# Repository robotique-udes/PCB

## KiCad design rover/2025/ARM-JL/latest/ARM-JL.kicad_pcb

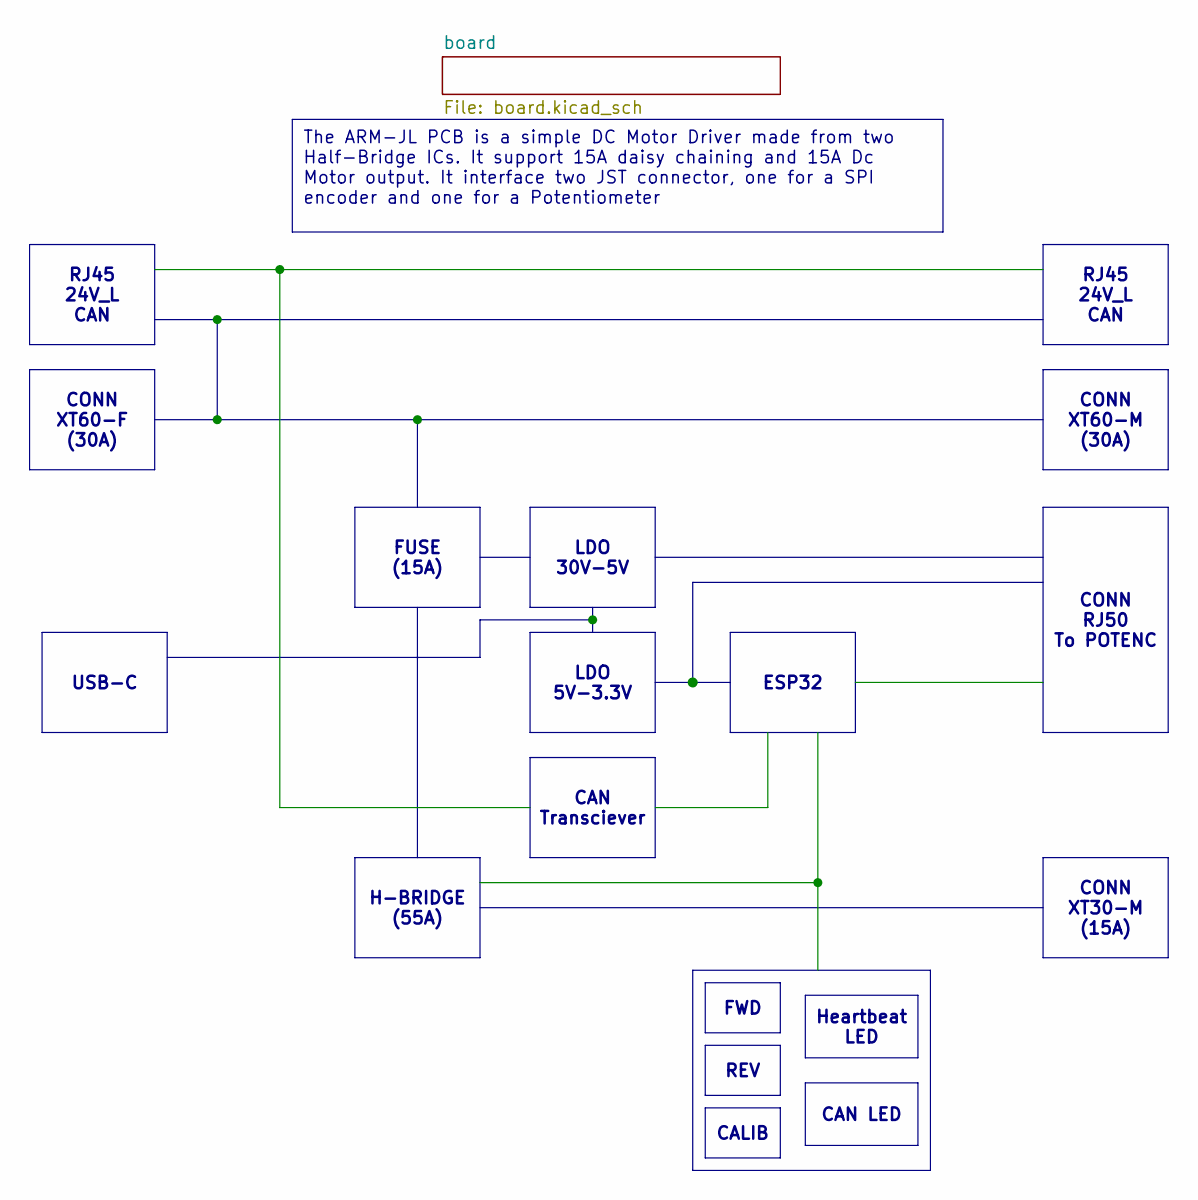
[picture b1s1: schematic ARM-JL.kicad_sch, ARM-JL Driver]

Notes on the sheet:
LDO 30V-5V
REV
CONN XT60-M (30A)
FWD
RJ45 24V_L CAN
FUSE (15A)
CAN LED
H-BRIDGE (55A)
Heartbeat LED
CONN XT60-F (30A)
CAN Transciever
USB-C
CONN RJ50 To POTENC
The ARM-JL PCB is a simple DC Motor Driver made from two Half-Bridge ICs. It support 15A daisy chaining and 15A Dc Motor output. It interface two JST connector, one for a SPI encoder and one for a Potentiometer
LDO 5V-3.3V
CALIB
ESP32
CONN XT30-M (15A)

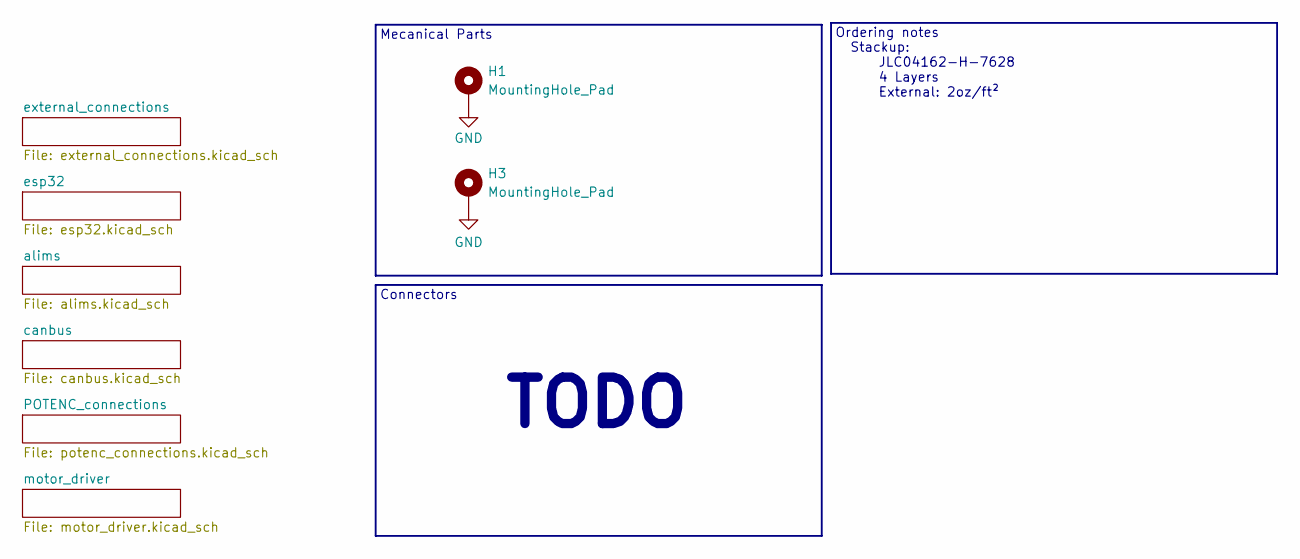
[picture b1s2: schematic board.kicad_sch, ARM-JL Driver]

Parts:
H1, H3: MountingHole_Pad; MountingHole_3.2mm_M3_DIN965_Pad_TopBottom

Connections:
GND: H1.1, H3.1; also elsewhere on the board

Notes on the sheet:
TODO
Mecanical Parts
Stackup: JLC04162-H-7628 4 Layers External: 2oz/ft²
Connectors
Ordering notes

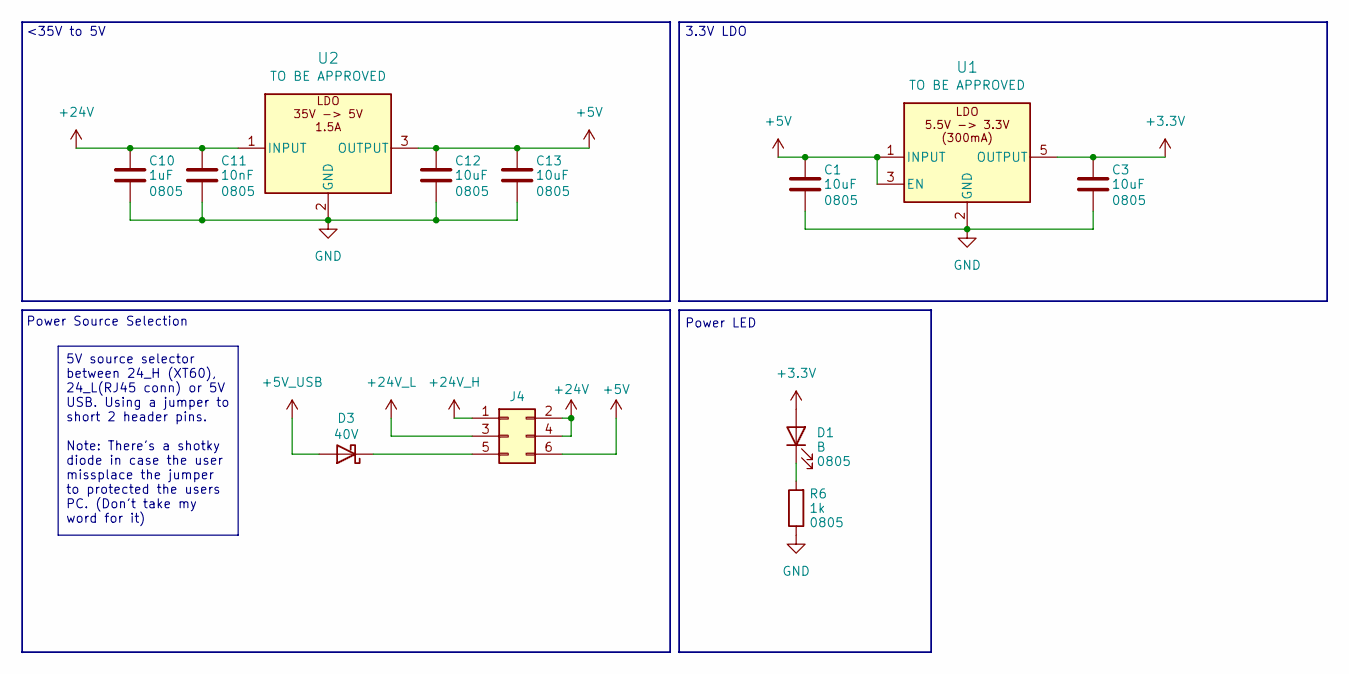
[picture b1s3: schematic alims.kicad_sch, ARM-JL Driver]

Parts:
C1, C3, C12, C13: 10uF; C_0805_2012Metric_Pad1.18x1.45mm_HandSolder
C10: 1uF; C_0805_2012Metric_Pad1.18x1.45mm_HandSolder
C11: 10nF; C_0805_2012Metric_Pad1.18x1.45mm_HandSolder
D1: B; LED_0805_2012Metric_Pad1.15x1.40mm_HandSolder
D3: 40V; D_SMA
J4: Conn_02x03_Odd_Even; PinHeader_2x03_P2.54mm_Vertical_SMD
R6: 1k; R_0805_2012Metric_Pad1.20x1.40mm_HandSolder
U1: LDO-TLV74033PDBVR; SOT-23-5_HandSoldering
U2: LDO-LM7805MPX/NOPB; SOT-223-3_TabPin2

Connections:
+5V: C1.1, C12.1, C13.1, J4.6, U1.1 (INPUT), U1.3 (EN), U2.3 (OUTPUT); also elsewhere on the board
+5V_USB: D3.2 (A); also elsewhere on the board
+24V: C10.1, C11.1, J4.2, J4.4, U2.1 (INPUT)
+24V_H: J4.1; also elsewhere on the board
+24V_L: J4.3; also elsewhere on the board
GND: C1.2, C3.2, C10.2, C11.2, C12.2, C13.2, R6.1, U1.2 (GND), U2.2 (GND); also elsewhere on the board
unnamed: D1.1 (K), R6.2
unnamed: D3.1 (K), J4.5

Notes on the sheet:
5V source selector between 24_H (XT60), 24_L(RJ45 conn) or 5V USB. Using a jumper to short 2 header pins. Note: There's a shotky diode in case the user missplace the jumper to protected the users PC. (Don't take my word for it)
3.3V LDO
Power LED
<35V to 5V
Power Source Selection

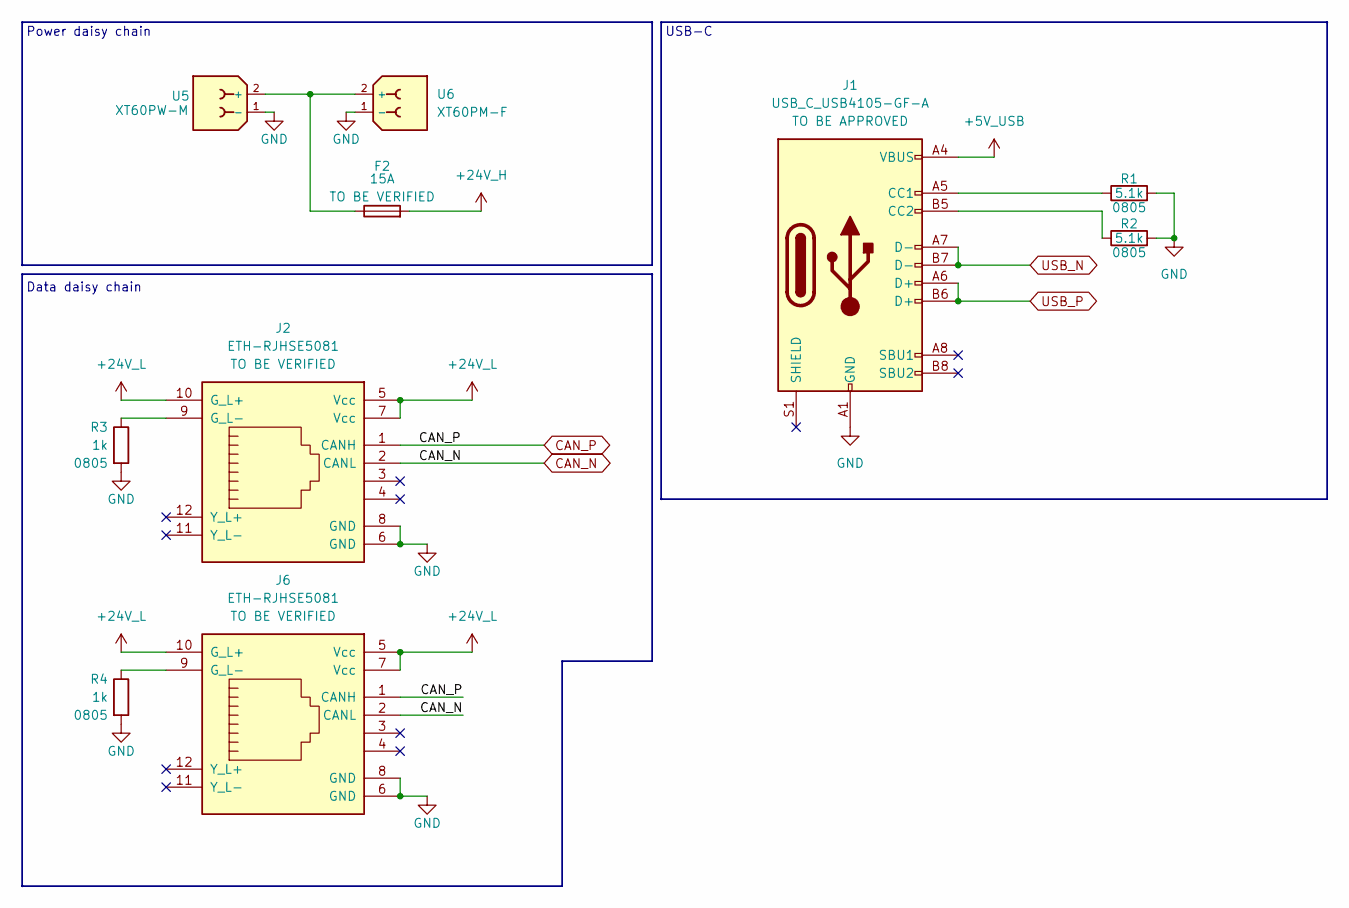
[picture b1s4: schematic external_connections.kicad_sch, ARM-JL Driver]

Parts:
F2: 15A; FuseHolder-3588-20
J1: USB_C_USB4105-GF-A; USB4145_GCT
J2, J6: ETH-RJHSE5081
R1, R2: 5.1k; R_0805_2012Metric_Pad1.20x1.40mm_HandSolder
R3, R4: 1k; R_0805_2012Metric_Pad1.20x1.40mm_HandSolder
U5: XT60PW-M; AMASS_XT60PW-M_1x02_P7.20mm_Horizontal
U6: XT60PM-F; AMASS_XT60PW-F_1x02_P7.20mm_Horizontal

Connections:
+5V_USB: J1.A4 (VBUS), J1.A9 (VBUS), J1.B4 (VBUS), J1.B9 (VBUS); also elsewhere on the board
+24V_H: F2.1; also elsewhere on the board
+24V_L: J2.5 (Vcc), J2.7 (Vcc), J2.10 (G_L+), J6.5 (Vcc), J6.7 (Vcc), J6.10 (G_L+); also elsewhere on the board
CAN_N: J2.2 (CANL), J6.2 (CANL); also elsewhere on the board
CAN_P: J2.1 (CANH), J6.1 (CANH); also elsewhere on the board
GND: J1.A1 (GND), J1.A12 (GND), J1.B1 (GND), J1.B12 (GND), J2.6 (GND), J2.8 (GND), J6.6 (GND), J6.8 (GND), R1.2, R2.2, R3.2, R4.2, U5.1 (-), U6.1 (-); also elsewhere on the board
unnamed: J1.A5 (CC1), R1.1
unnamed: J1.B5 (CC2), R2.1
unnamed: J2.9 (G_L-), R3.1
unnamed: J6.9 (G_L-), R4.1
unnamed: F2.2, U5.2 (+), U6.2 (+)
USB_N: J1.A7 (D-), J1.B7 (D-); also elsewhere on the board
USB_P: J1.A6 (D+), J1.B6 (D+); also elsewhere on the board

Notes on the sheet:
Data daisy chain
USB-C
Power daisy chain

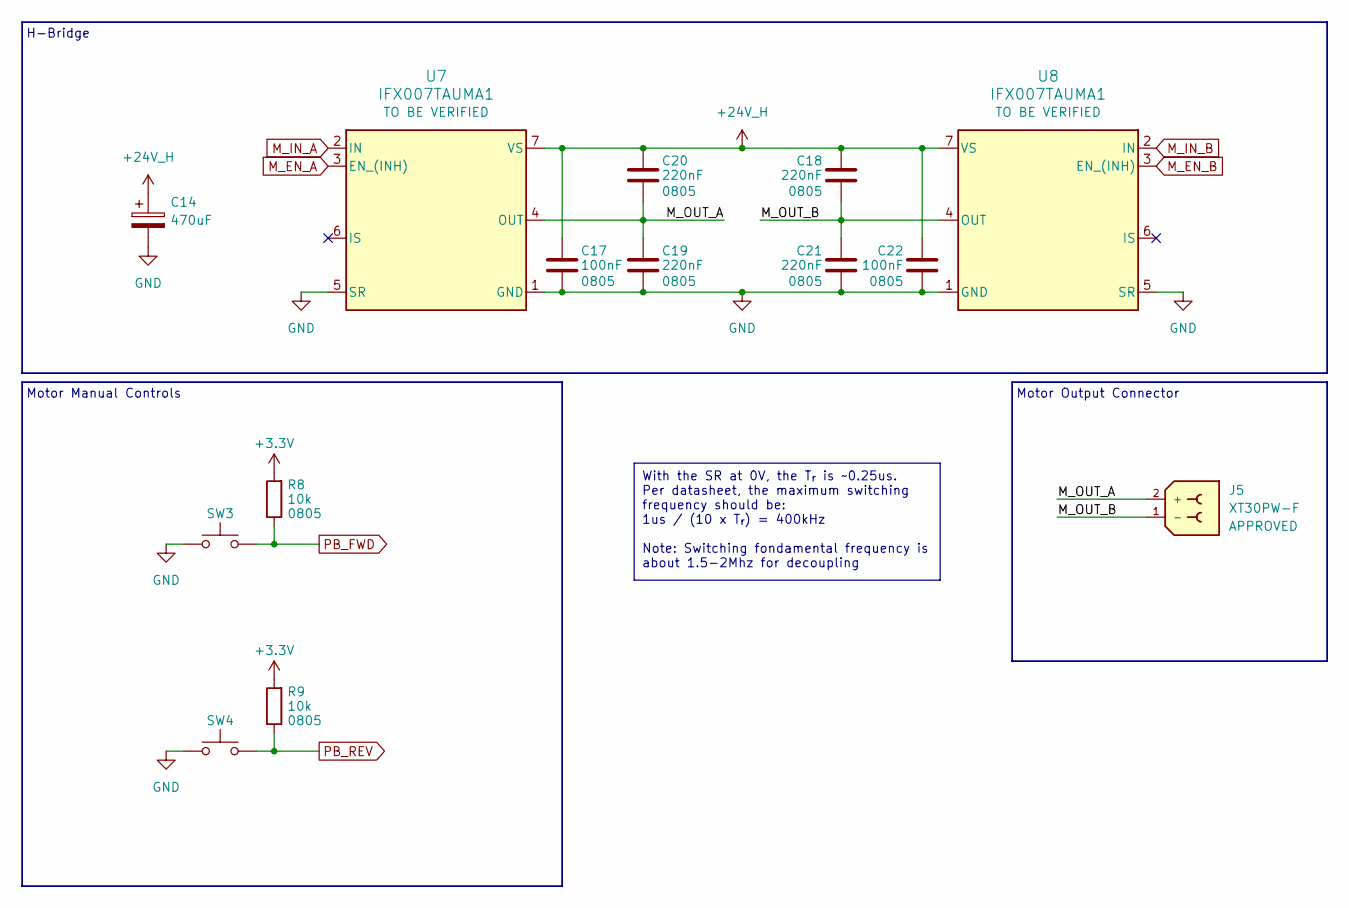
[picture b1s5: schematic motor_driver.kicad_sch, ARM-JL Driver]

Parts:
C14: 470uF; CP_Elec_10x12.6
C17, C22: 100nF; C_0805_2012Metric_Pad1.18x1.45mm_HandSolder
C18, C19, C20, C21: 220nF; C_0805_2012Metric_Pad1.18x1.45mm_HandSolder
J5: XT30PW-F; AMASS_XT30PW-F_1x02_P2.50mm_Horizontal; PARTREV 1.2
R8, R9: 10k; R_0805_2012Metric_Pad1.20x1.40mm_HandSolder
SW3, SW4: SW-PTS815SJM250SMTRLFS; SW-PTS815 SJM250SMTRLFS
U7, U8: IFX007TAUMA1; TO-263-7_TabPin4

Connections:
+24V_H: C14.1, C17.1, C18.1, C20.1, C22.1, U7.7 (VS), U8.7 (VS); also elsewhere on the board
/board/motor_driver/M_OUT_A: C19.1, C20.2, J5.2 (+), U7.4 (OUT)
/board/motor_driver/M_OUT_B: C18.2, C21.1, J5.1 (-), U8.4 (OUT)
GND: C14.2, C17.2, C19.2, C21.2, C22.2, SW3.1, SW3.2, SW4.1, SW4.2, U7.1 (GND), U7.5 (SR), U8.1 (GND), U8.5 (SR); also elsewhere on the board
M_EN_A: U7.3 (EN_(INH)); also elsewhere on the board
M_EN_B: U8.3 (EN_(INH)); also elsewhere on the board
M_IN_A: U7.2 (IN); also elsewhere on the board
M_IN_B: U8.2 (IN); also elsewhere on the board
PB_FWD: R8.1, SW3.4; also elsewhere on the board
PB_REV: R9.1, SW4.4; also elsewhere on the board

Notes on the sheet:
With the SR at 0V, the T_{r} is ~0.25us. Per datasheet, the maximum switching frequency should be: 1us / (10 x T_{r}) = 400kHz Note: Switching fondamental frequency is about 1.5-2Mhz for decoupling
Motor Manual Controls
H-Bridge
Motor Output Connector

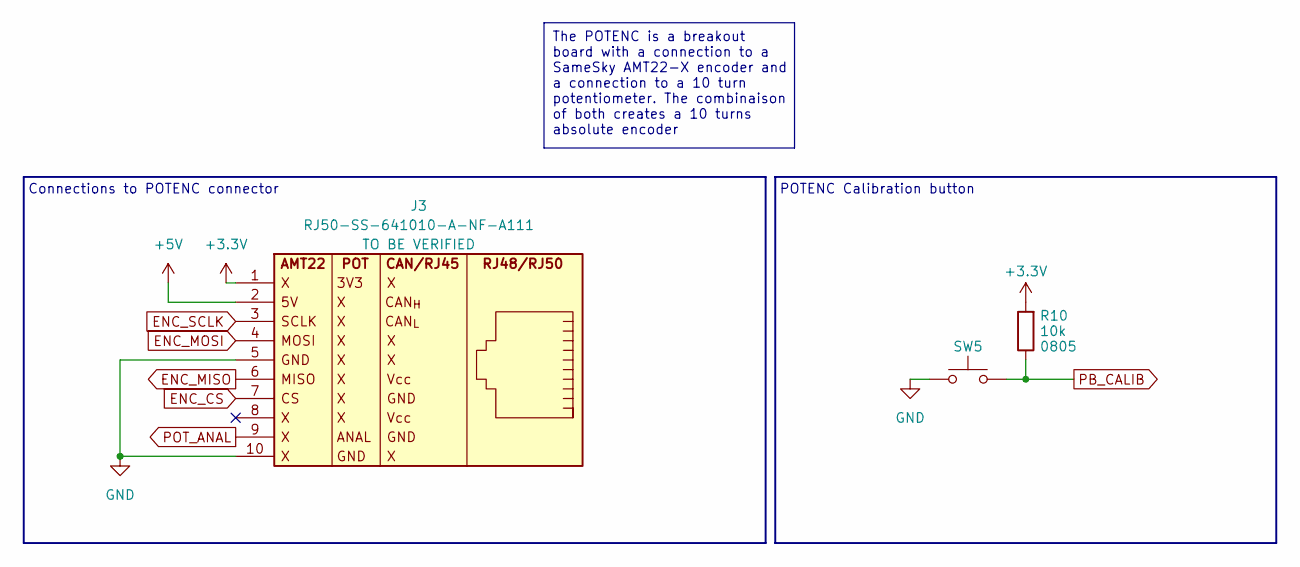
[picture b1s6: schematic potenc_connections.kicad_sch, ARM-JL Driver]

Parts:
J3: RJ50-SS-641010-A-NF-A111
R10: 10k; R_0805_2012Metric_Pad1.20x1.40mm_HandSolder
SW5: SW-PTS815SJM250SMTRLFS; SW-PTS815 SJM250SMTRLFS

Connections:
+5V: J3.2; also elsewhere on the board
ENC_CS: J3.7; also elsewhere on the board
ENC_MISO: J3.6; also elsewhere on the board
ENC_MOSI: J3.4; also elsewhere on the board
ENC_SCLK: J3.3; also elsewhere on the board
GND: J3.5, J3.10, SW5.1, SW5.2; also elsewhere on the board
PB_CALIB: R10.1, SW5.4; also elsewhere on the board
POT_ANAL: J3.9; also elsewhere on the board

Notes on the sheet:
The POTENC is a breakout board with a connection to a SameSky AMT22-X encoder and a connection to a 10 turn potentiometer. The combinaison of both creates a 10 turns absolute encoder
Connections to POTENC connector
POTENC Calibration button

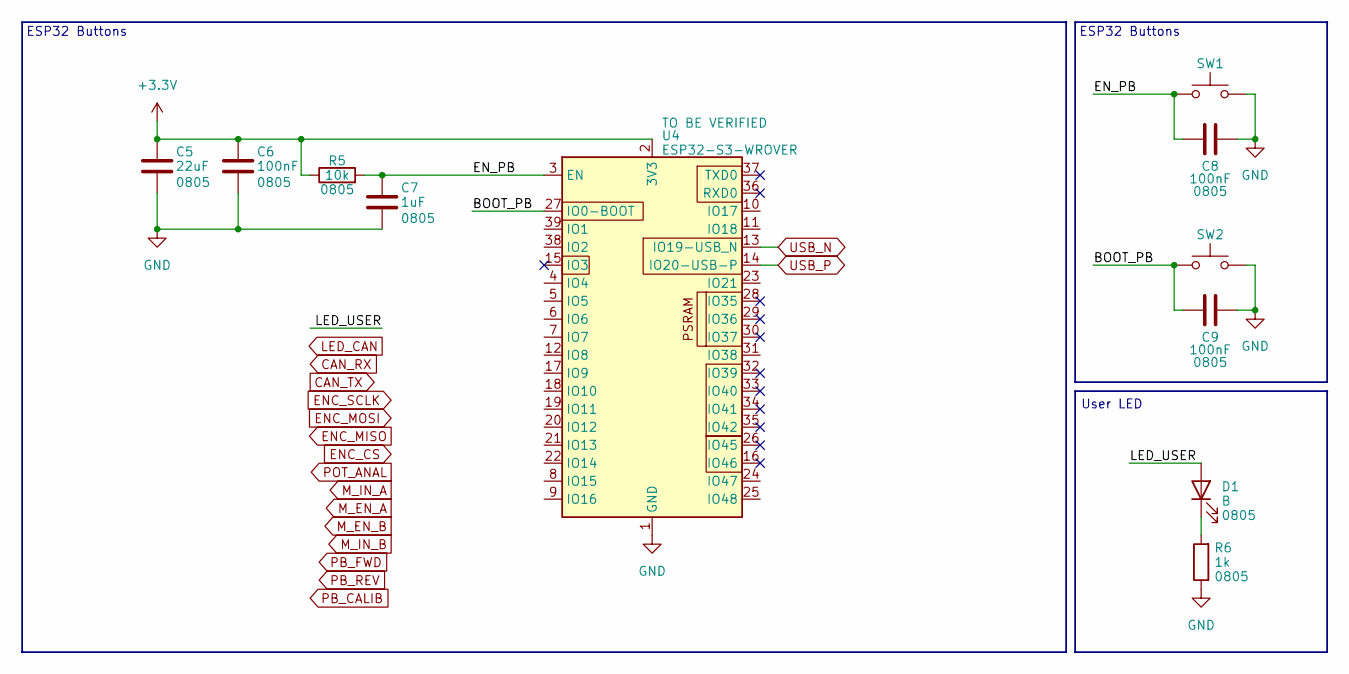
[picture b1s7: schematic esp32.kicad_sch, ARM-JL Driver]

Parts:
C5: 22uF; C_0805_2012Metric_Pad1.18x1.45mm_HandSolder
C6, C8, C9: 100nF; C_0805_2012Metric_Pad1.18x1.45mm_HandSolder
C7: 1uF; C_0805_2012Metric_Pad1.18x1.45mm_HandSolder
D1: B; LED_0805_2012Metric_Pad1.15x1.40mm_HandSolder
R5: 10k; R_0805_2012Metric_Pad1.20x1.40mm_HandSolder
R6: 1k; R_0805_2012Metric_Pad1.20x1.40mm_HandSolder
SW1, SW2: SW-PTS815SJM250SMTRLFS; SW-PTS815 SJM250SMTRLFS
U4: ESP32-S3-WROVER; ESP32-S3-WROOM-1U

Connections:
/board/esp32/BOOT_PB: C9.2, SW2.1, SW2.2, U4.27 (IO0-BOOT)
/board/esp32/EN_PB: C7.1, C8.2, R5.2, SW1.1, SW1.2, U4.3 (EN)
CAN_RX: U4.17 (IO9); also elsewhere on the board
CAN_TX: U4.18 (IO10); also elsewhere on the board
ENC_CS: U4.7 (IO7); also elsewhere on the board
ENC_MISO: U4.4 (IO4); also elsewhere on the board
ENC_MOSI: U4.5 (IO5); also elsewhere on the board
ENC_SCLK: U4.6 (IO6); also elsewhere on the board
GND: C5.2, C6.2, C7.2, C8.1, C9.1, R6.1, SW1.4, SW2.4, U4.1 (GND), U4.40 (GND), U4.41 (GND); also elsewhere on the board
LED_CAN: U4.23 (IO21); also elsewhere on the board
M_EN_A: U4.38 (IO2); also elsewhere on the board
M_EN_B: U4.24 (IO47); also elsewhere on the board
M_IN_A: U4.39 (IO1); also elsewhere on the board
M_IN_B: U4.25 (IO48); also elsewhere on the board
unnamed: D1.1 (K), R6.2
PB_CALIB: U4.21 (IO13); also elsewhere on the board
PB_FWD: U4.22 (IO14); also elsewhere on the board
PB_REV: U4.31 (IO38); also elsewhere on the board
POT_ANAL: U4.8 (IO15); also elsewhere on the board
USB_N: U4.13 (IO19-USB_N); also elsewhere on the board
USB_P: U4.14 (IO20-USB-P); also elsewhere on the board

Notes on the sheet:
User LED
ESP32 Buttons

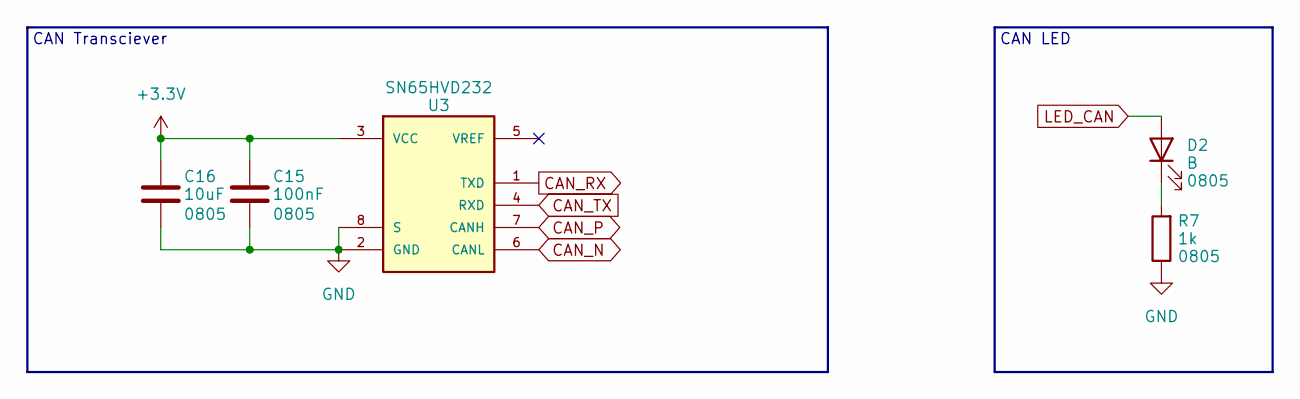
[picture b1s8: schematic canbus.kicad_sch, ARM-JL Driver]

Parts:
C15: 100nF; C_0805_2012Metric_Pad1.18x1.45mm_HandSolder
C16: 10uF; C_0805_2012Metric_Pad1.18x1.45mm_HandSolder
D2: B; LED_0805_2012Metric_Pad1.15x1.40mm_HandSolder
R7: 1k; R_0805_2012Metric_Pad1.20x1.40mm_HandSolder
U3: SN65HVD232; SOIC-8_3.9x4.9mm_P1.27mm; PARTREV 4

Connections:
CAN_N: U3.6 (CANL); also elsewhere on the board
CAN_P: U3.7 (CANH); also elsewhere on the board
CAN_RX: U3.1 (TXD); also elsewhere on the board
CAN_TX: U3.4 (RXD); also elsewhere on the board
GND: C15.2, C16.2, R7.1, U3.2 (GND), U3.8 (S); also elsewhere on the board
LED_CAN: D2.2 (A); also elsewhere on the board
unnamed: D2.1 (K), R7.2

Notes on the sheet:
CAN Transciever
CAN LED

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
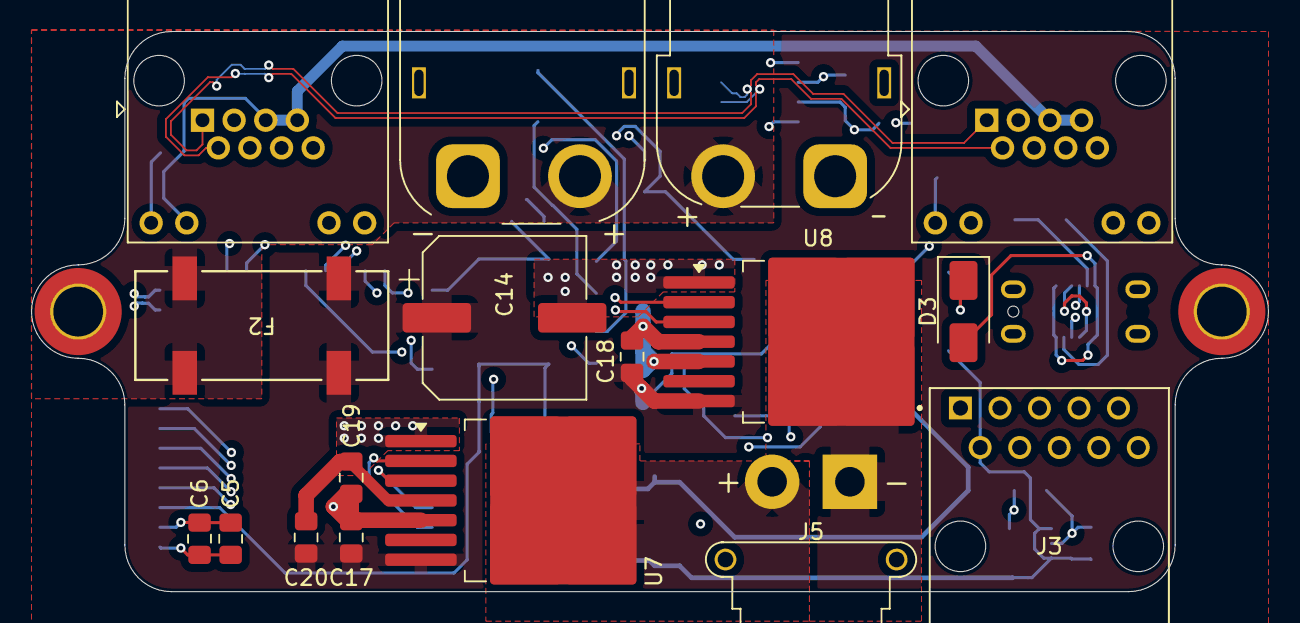
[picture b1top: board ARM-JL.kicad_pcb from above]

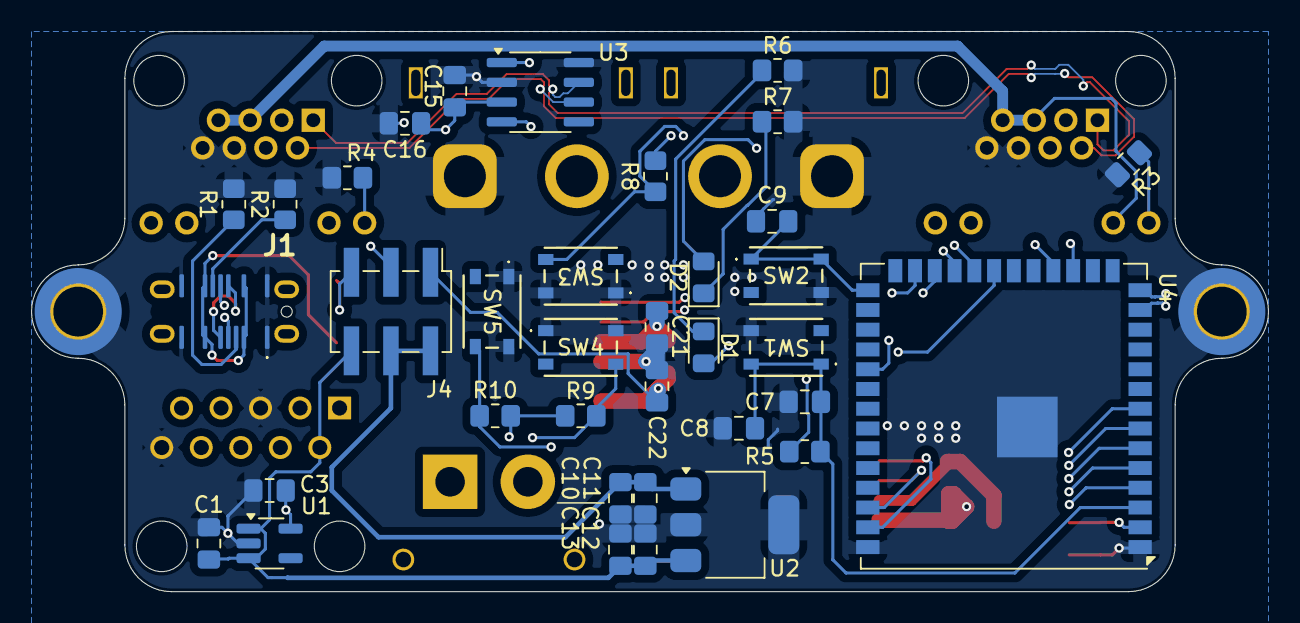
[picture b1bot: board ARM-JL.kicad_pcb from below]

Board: 4 copper layers, 79.5 x 36.0 mm, 55 parts (36 on the bottom side), 38 nets.

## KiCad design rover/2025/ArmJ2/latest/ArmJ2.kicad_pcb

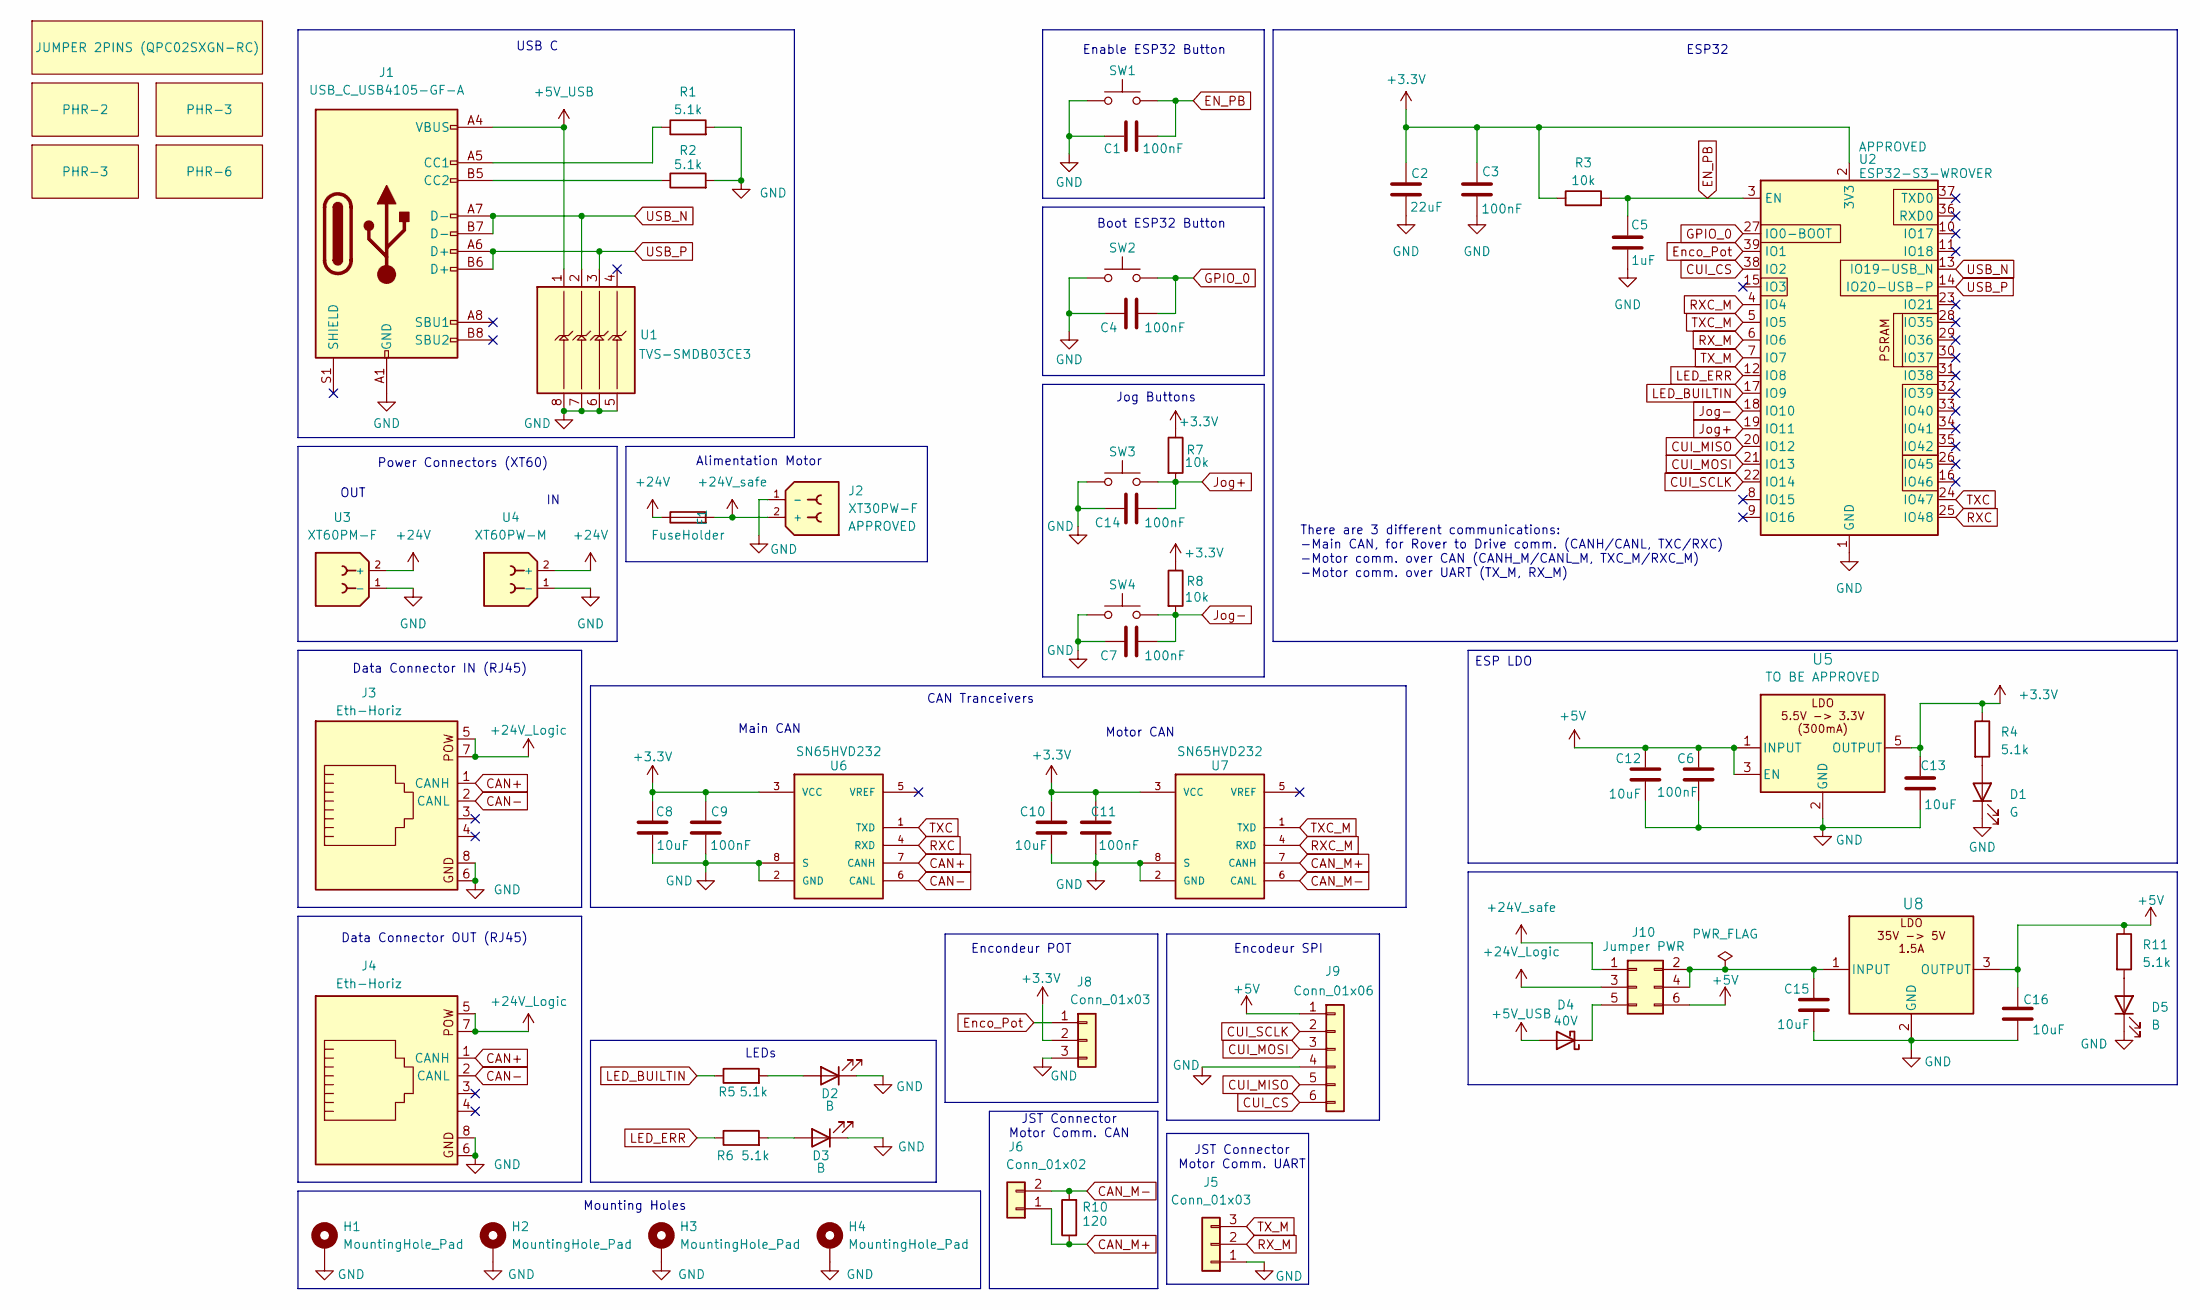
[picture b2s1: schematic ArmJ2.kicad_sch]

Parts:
C1, C3, C4, C6, C7, C9, C11, C14: 100nF; C_0805_2012Metric_Pad1.18x1.45mm_HandSolder
C2: 22uF; C_0805_2012Metric_Pad1.18x1.45mm_HandSolder
C5: 1uF; C_0805_2012Metric_Pad1.18x1.45mm_HandSolder
C8, C10, C12, C13, C15, C16: 10uF; C_0805_2012Metric_Pad1.18x1.45mm_HandSolder
D1: G; LED_0805_2012Metric_Pad1.15x1.40mm_HandSolder
D2, D3, D5: B; LED_0805_2012Metric_Pad1.15x1.40mm_HandSolder
D4: 40V; D_SMA
F1: FuseHolder; FUSE_3568-20
G1, G6: PHR-3
G3: JUMPER 2PINS (QPC02SXGN-RC)
G4: PHR-2
G8: PHR-6
H1, H2, H3, H4: MountingHole_Pad; MountingHole_3.2mm_M3_DIN965_Pad_TopBottom
J1: USB_C_USB4105-GF-A; USB_C_Receptacle_GCT_USB4105-xx-A_16P_TopMnt_Horizontal
J2: XT30PW-F; AMASS_XT30PW-F_1x02_P2.50mm_Horizontal; PARTREV 1.2
J3, J4: Eth-Horiz; Ethernet_Horizontal
J5: Conn_01x03; JST_PH_S3B-PH-K_1x03_P2.00mm_Horizontal
J6: Conn_01x02; JST_PH_S2B-PH-K_1x02_P2.00mm_Horizontal
J8: Conn_01x03; JST_PH_B3B-PH-K_1x03_P2.00mm_Vertical
J9: Conn_01x06; JST_PH_B6B-PH-K_1x06_P2.00mm_Vertical
J10: Jumper PWR; PinHeader_2x03_P2.54mm_Vertical
R1, R2, R4, R5, R6, R11: 5.1k; R_0805_2012Metric_Pad1.20x1.40mm_HandSolder
R3, R7, R8: 10k; R_0805_2012Metric_Pad1.20x1.40mm_HandSolder
R10: 120; R_0805_2012Metric_Pad1.20x1.40mm_HandSolder
SW1, SW2, SW3, SW4: SW-PTS815SJM250SMTRLFS; SW-PTS815 SJM250SMTRLFS
U1: TVS-SMDB03CE3; SOIC-8_3.9x4.9mm_P1.27mm
U2: ESP32-S3-WROVER; ESP32-S3-WROOM-1U
U3: XT60PM-F; AMASS_XT60PW-F_1x02_P7.20mm_Horizontal
U4: XT60PW-M; AMASS_XT60PW-M_1x02_P7.20mm_Horizontal
U5: LDO-TLV74033PDBVR; SOT-23-5_HandSoldering
U6, U7: SN65HVD232; SOIC-8_3.9x4.9mm_P1.27mm; PARTREV 4
U8: LDO-LM7805MPX/NOPB; SOT-223-3_TabPin2

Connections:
+3.3V: C2.1, C3.1, C8.1, C9.1, C10.1, C11.1, C13.1, J8.2, R3.1, R4.1, R7.1, R8.1, U2.2 (3V3), U5.5 (OUTPUT), U6.3 (VCC), U7.3 (VCC)
+5V: C6.1, C12.1, C16.1, J9.1, J10.6, R11.1, U5.1 (INPUT), U5.3 (EN), U8.3 (OUTPUT)
+5V_USB: D4.2 (A), J1.A4 (VBUS), J1.A9 (VBUS), J1.B4 (VBUS), J1.B9 (VBUS), U1.1
+24V: F1.2, U3.2 (+), U4.2 (+)
+24V_Logic: J3.5, J3.7, J4.5, J4.7, J10.3
+24V_safe: F1.1, J2.2 (+), J10.1
CAN+: J3.1 (CANH), J4.1 (CANH), U6.7 (CANH)
CAN-: J3.2 (CANL), J4.2 (CANL), U6.6 (CANL)
CAN_M+: J6.1, R10.1, U7.7 (CANH)
CAN_M-: J6.2, R10.2, U7.6 (CANL)
CUI_CS: J9.6, U2.38 (IO2)
CUI_MISO: J9.5, U2.20 (IO12)
CUI_MOSI: J9.3, U2.21 (IO13)
CUI_SCLK: J9.2, U2.22 (IO14)
EN_PB: C1.2, C5.1, R3.2, SW1.4, U2.3 (EN)
Enco_Pot: J8.1, U2.39 (IO1)
GND: C1.1, C2.2, C3.2, C4.1, C5.2, C6.2, C7.1, C8.2, C9.2, C10.2, C11.2, C12.2, C13.2, C14.1, C15.2, C16.2, D1.1 (K), D2.1 (K), D3.1 (K), D5.1 (K), H1.1, H2.1, H3.1, H4.1, J1.A1 (GND), J1.A12 (GND), J1.B1 (GND), J1.B12 (GND), J2.1 (-), J3.6, J3.8, J4.6, J4.8, J5.1, J8.3, J9.4, R1.2, R2.2, SW1.1, SW1.2, SW2.1, SW2.2, SW3.1, SW3.2, SW4.1, SW4.2, U1.5, U1.6, U1.7, U1.8, U2.1 (GND), U2.40 (GND), U2.41 (GND), U3.1 (-), U4.1 (-), U5.2 (GND), U6.2 (GND), U6.8 (S), U7.2 (GND), U7.8 (S), U8.2 (GND)
GPIO_0: C4.2, SW2.4, U2.27 (IO0-BOOT)
Jog+: C14.2, R7.2, SW3.4, U2.19 (IO11)
Jog-: C7.2, R8.2, SW4.4, U2.18 (IO10)
LED_BUILTIN: R5.1, U2.17 (IO9)
LED_ERR: R6.1, U2.12 (IO8)
unnamed: D1.2 (A), R4.2
unnamed: D2.2 (A), R5.2
unnamed: D3.2 (A), R6.2
unnamed: D4.1 (K), J10.5
unnamed: D5.2 (A), R11.2
unnamed: J1.A5 (CC1), R1.1
unnamed: J1.B5 (CC2), R2.1
unnamed: C15.1, J10.2, J10.4, U8.1 (INPUT)
RXC: U2.25 (IO48), U6.4 (RXD)
RXC_M: U2.4 (IO4), U7.4 (RXD)
RX_M: J5.2, U2.6 (IO6)
TXC: U2.24 (IO47), U6.1 (TXD)
TXC_M: U2.5 (IO5), U7.1 (TXD)
TX_M: J5.3, U2.7 (IO7)
USB_N: J1.A7 (D-), J1.B7 (D-), U1.2, U2.13 (IO19-USB_N)
USB_P: J1.A6 (D+), J1.B6 (D+), U1.3, U2.14 (IO20-USB-P)

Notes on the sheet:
ESP32
Data Connector IN (RJ45)
OUT
Mounting Holes
Encodeur SPI
Power Connectors (XT60)
JST Connector Motor Comm. UART
Main CAN
Motor CAN
There are 3 different communications: -Main CAN, for Rover to Drive comm. (CANH/CANL, TXC/RXC) -Motor comm. over CAN (CANH_M/CANL_M, TXC_M/RXC_M) -Motor comm. over UART (TX_M, RX_M)
ESP LDO
Alimentation Motor
Boot ESP32 Button
Jog Buttons
Enable ESP32 Button
CAN Tranceivers
Data Connector OUT (RJ45)
USB C
LEDs
Encondeur POT
JST Connector Motor Comm. CAN

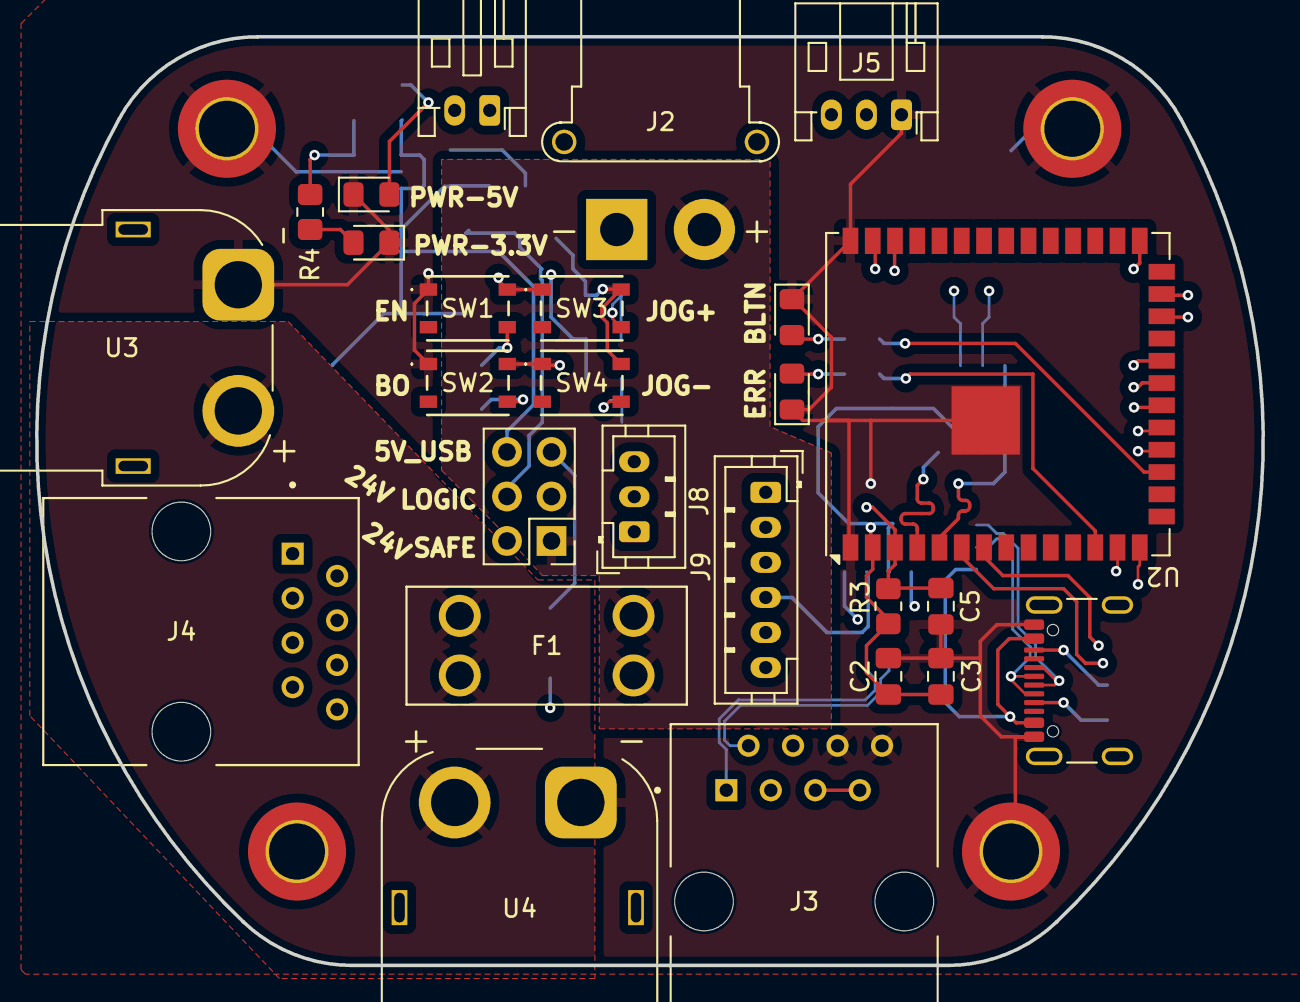
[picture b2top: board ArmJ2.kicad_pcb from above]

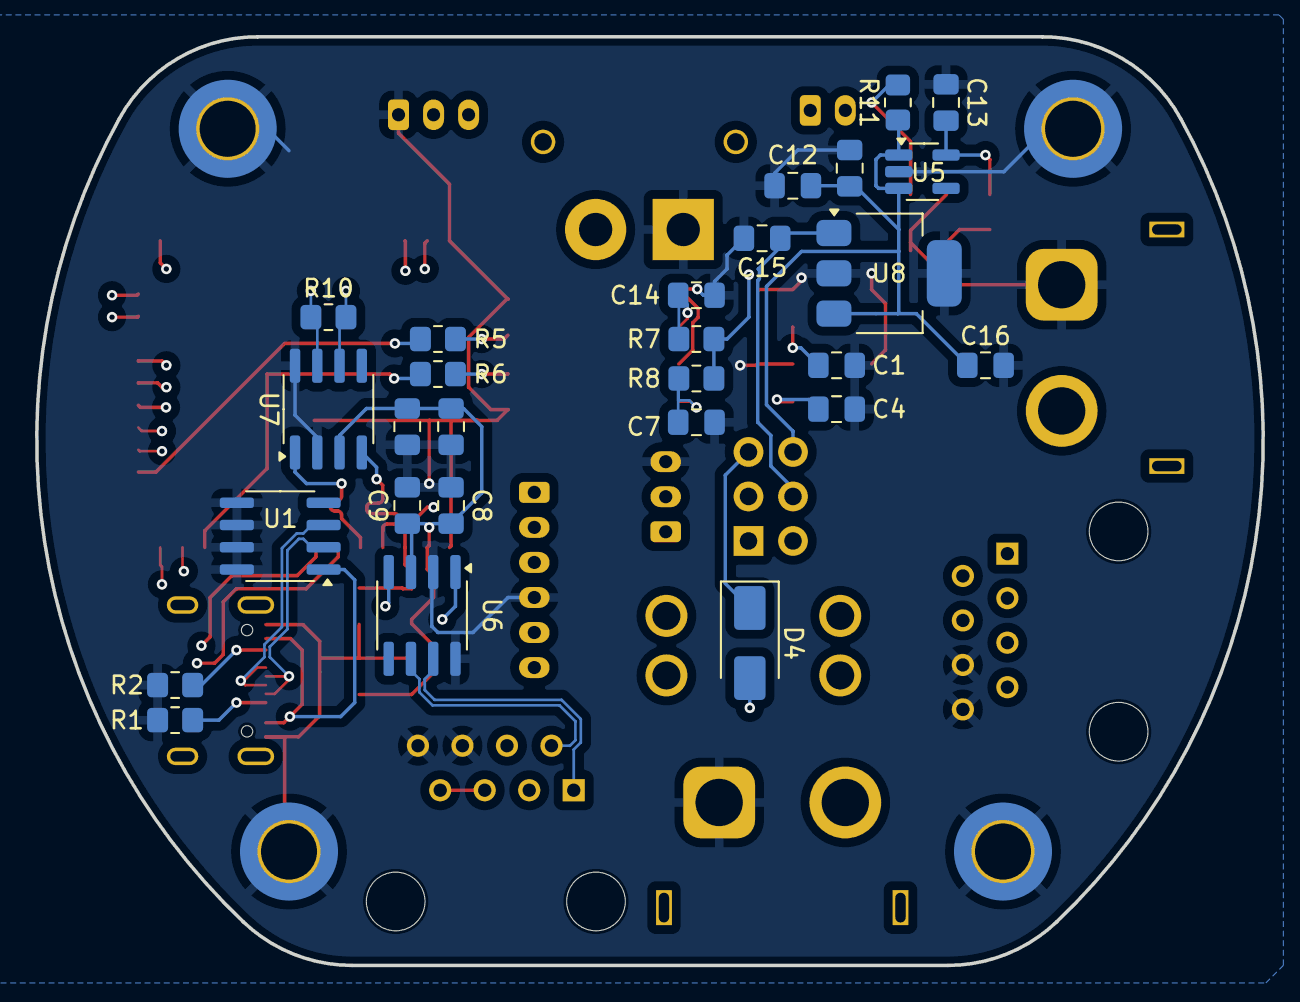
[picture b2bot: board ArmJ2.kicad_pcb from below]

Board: 4 copper layers, 70.0 x 53.0 mm, 57 parts (27 on the bottom side), 38 nets.
